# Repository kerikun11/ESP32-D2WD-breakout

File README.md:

# ESP32-D2WD-breakout
a breakout board for ESP32-D2WD

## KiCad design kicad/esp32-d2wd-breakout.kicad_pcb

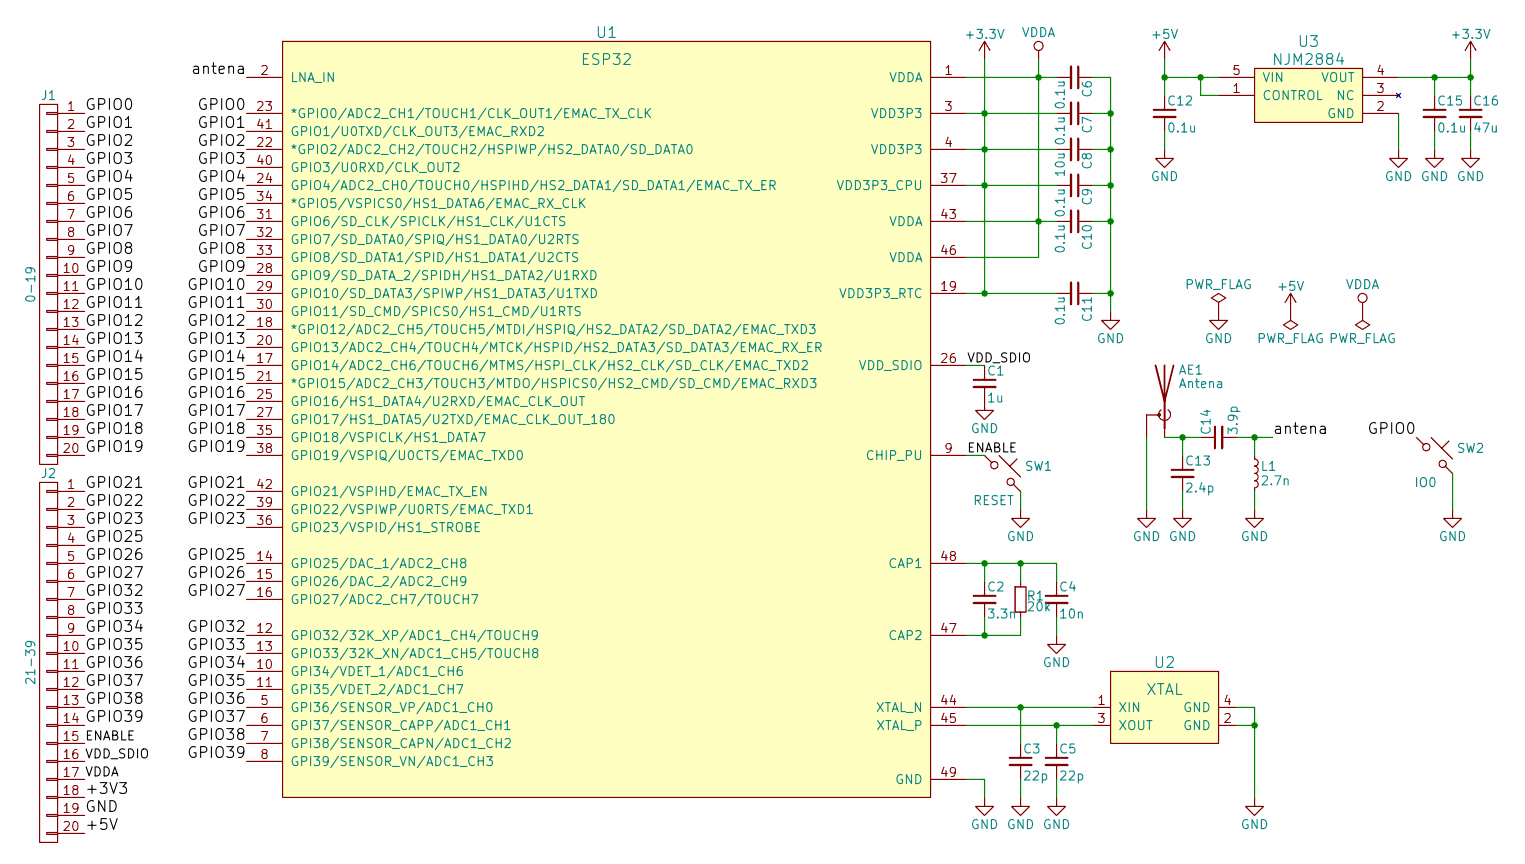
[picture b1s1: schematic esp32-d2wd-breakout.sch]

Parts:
AE1: Antena; ANT
C1: 1u; C_0402
C2: 3.3n; C_0402
C3, C5: 22p; C_0402
C4: 10n; C_0402
C6, C7, C9, C10, C11, C12, C15: 0.1u; C_0402
C8: 10u; C_0603
C13: 2.4p; C_0402
C14: 3.9p; C_0402
C16: 47u; C_0805
J1: 0-19; Pin_Header_Straight_1x20_Pitch2.54mm
J2: 21-39; Pin_Header_Straight_1x20_Pitch2.54mm
L1: 2.7n; L_0402
R1: 20k; R_0402
SW1: RESET; SW_PUSH
SW2: IO0; SW_PUSH
U1: ESP32; QFN-48-1EP_5x5mm_Pitch0.35mm
U2: XTAL; Crystal_SMD_SeikoEpson_FA238-4pin_3.2x2.5mm
U3: NJM2884; SOT89-5_Housing

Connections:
+5V: C12.1, J2.20, U3.1 (CONTROL), U3.5 (VIN)
/ENABLE: J2.15, SW1.1, U1.9 (CHIP_PU)
/GPIO0: J1.1, SW2.1, U1.23 (*GPIO0/ADC2_CH1/TOUCH1/CLK_OUT1/EMAC_TX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)
/GPIO1: J1.2, U1.41 (GPIO1/U0TXD/CLK_OUT3/EMAC_RXD2)
/GPIO2: J1.3, U1.22 (*GPIO2/ADC2_CH2/TOUCH2/HSPIWP/HS2_DATA0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)
/GPIO3: J1.4, U1.40 (GPIO3/U0RXD/CLK_OUT2)
/GPIO4: J1.5, U1.24 (GPIO4/ADC2_CH0/TOUCH0/HSPIHD/HS2_DATA1/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)
/GPIO5: J1.6, U1.34 (*GPIO5/VSPICS0/HS1_DATA6/EMAC_RX_CLK)
/GPIO6: J1.7, U1.31 (GPIO6/SD_CLK/SPICLK/HS1_CLK/U1CTS)
/GPIO7: J1.8, U1.32 (GPIO7/SD_DATA0/SPIQ/HS1_DATA0/U2RTS)
/GPIO8: J1.9, U1.33 (GPIO8/SD_DATA1/SPID/HS1_DATA1/U2CTS)
/GPIO9: J1.10, U1.28 (GPIO9/SD_DATA_2/SPIDH/HS1_DATA2/U1RXD)
/GPIO10: J1.11, U1.29 (GPIO10/SD_DATA3/SPIWP/HS1_DATA3/U1TXD)
/GPIO11: J1.12, U1.30 (GPIO11/SD_CMD/SPICS0/HS1_CMD/U1RTS)
/GPIO12: J1.13, U1.18 (*GPIO12/ADC2_CH5/TOUCH5/MTDI/HSPIQ/HS2_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)
/GPIO13: J1.14, U1.20 (GPIO13/ADC2_CH4/TOUCH4/MTCK/HSPID/HS2_D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)
/GPIO14: J1.15, U1.17 (GPIO14/ADC2_CH6/TOUCH6/MTMS/HSPI_CLK/HS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)
/GPIO15: J1.16, U1.21 (*GPIO15/ADC2_CH3/TOUCH3/MTDO/HSPICS0/HS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)
/GPIO16: J1.17, U1.25 (GPIO16/HS1_DATA4/U2RXD/EMAC_CLK_OUT)
/GPIO17: J1.18, U1.27 (GPIO17/HS1_DATA5/U2TXD/EMAC_CLK_OUT_180)
/GPIO18: J1.19, U1.35 (GPIO18/VSPICLK/HS1_DATA7)
/GPIO19: J1.20, U1.38 (GPIO19/VSPIQ/U0CTS/EMAC_TXD0)
/GPIO21: J2.1, U1.42 (GPIO21/VSPIHD/EMAC_TX_EN)
/GPIO22: J2.2, U1.39 (GPIO22/VSPIWP/U0RTS/EMAC_TXD1)
/GPIO23: J2.3, U1.36 (GPIO23/VSPID/HS1_STROBE)
/GPIO25: J2.4, U1.14 (GPIO25/DAC_1/ADC2_CH8)
/GPIO26: J2.5, U1.15 (GPIO26/DAC_2/ADC2_CH9)
/GPIO27: J2.6, U1.16 (GPIO27/ADC2_CH7/TOUCH7)
/GPIO32: J2.7, U1.12 (GPIO32/32K_XP/ADC1_CH4/TOUCH9)
/GPIO33: J2.8, U1.13 (GPIO33/32K_XN/ADC1_CH5/TOUCH8)
/GPIO34: J2.9, U1.10 (GPI34/VDET_1/ADC1_CH6)
/GPIO35: J2.10, U1.11 (GPI35/VDET_2/ADC1_CH7)
/GPIO36: J2.11, U1.5 (GPI36/SENSOR_VP/ADC1_CH0)
/GPIO37: J2.12, U1.6 (GPI37/SENSOR_CAPP/ADC1_CH1)
/GPIO38: J2.13, U1.7 (GPI38/SENSOR_CAPN/ADC1_CH2)
/GPIO39: J2.14, U1.8 (GPI39/SENSOR_VN/ADC1_CH3)
/VDD_SDIO: C1.1, J2.16, U1.26 (VDD_SDIO)
/antena: C14.2, L1.1, U1.2 (LNA_IN)
GND: AE1.2 (Shield), C1.2, C3.2, C4.2, C5.2, C6.1, C7.1, C8.1, C9.1, C10.1, C11.1, C12.2, C13.2, C15.2, C16.2, J2.19, L1.2, SW1.2, SW2.2, U1.49 (GND), U2.2 (GND), U2.4 (GND), U3.2 (GND)
unnamed: AE1.1 (A), C13.1, C14.1
unnamed: C2.1, C4.1, R1.1, U1.48 (CAP1)
unnamed: C2.2, R1.2, U1.47 (CAP2)
unnamed: C3.1, U1.44 (XTAL_N), U2.1 (XIN)
unnamed: C5.1, U1.45 (XTAL_P), U2.3 (XOUT)
VDDA: C6.2, C10.2, J2.17, U1.1 (VDDA), U1.43 (VDDA), U1.46 (VDDA)

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
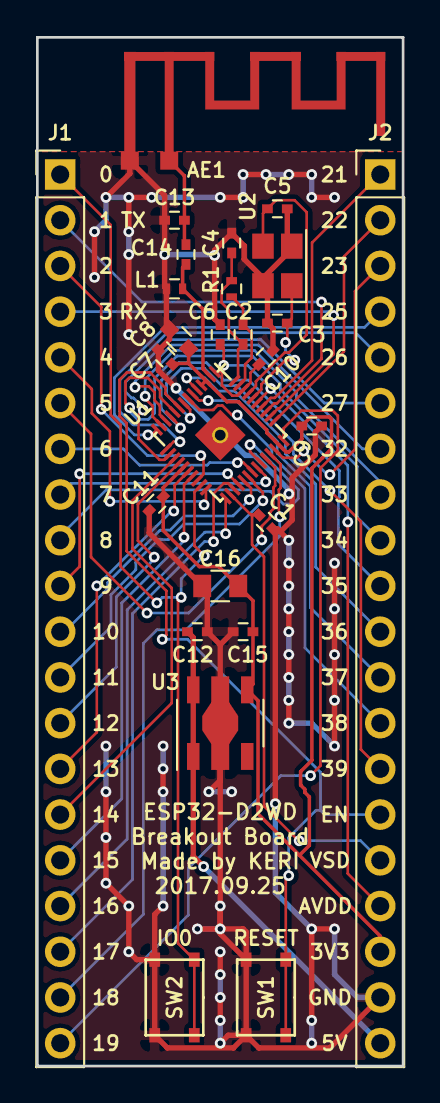
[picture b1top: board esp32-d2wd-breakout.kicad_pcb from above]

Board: 2 copper layers, 20.3 x 57.1 mm, 26 parts (0 on the bottom side), 46 nets.

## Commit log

2018-11-12 kicadファイルを追加
